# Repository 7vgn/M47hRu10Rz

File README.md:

# A Ruler with some mathematical extras

This is more than a regular ruler. It contains four mathematical topics from algebra, geometry, and other areas. Check out the [companion booklet](https://7vgn.github.io/M47hRu10Rz/). 

## Bill of Materials

| Ref | Qty | Part | Value | Links[^links]
| --- | ---:| --- | --- | --- |
| - | 1 | PCB | 2-layer, 0.8mm thickness, white soldermask, lead-free HASL | [J](https://jlcpcb.com/)
| C1 | 1 | Capacitor | SMD 1206, 100nF, X7R | [M](https://www.mouser.com/ProductDetail/?qs=Jm2GQyTW%2Fbgjukwx9JJFzw%3D%3D) [D](https://www.digikey.com/en/products/detail/kyocera-avx/KGM31DR72A104KU/563639?s=N4IgTCBcDaIIxgAwDY4GE6ICwGkCCAKmHiALoC%2BQA) [R](https://www.reichelt.de/shop/produkt/mlcc_1206_100_nf_100_v_-10_x7r-409241)
| D1..4 | 4 | LED | SMD 1206 (3216), green | [M](https://www.mouser.com/ProductDetail/?qs=kIhwFMorz7OTw%252BezAWlXhg%3D%3D) [D](https://www.digikey.com/en/products/detail/liteon/LTST-C150GKT/269216?s=N4IgTCBcDaIDIBUDKCC0BhAjAVgAwHEBpBEAXQF8g) [R](https://www.reichelt.de/shop/produkt/led_smd_1206_gruen_500_mcd_120_-361549)
| Q1[^polprot] | 1 | P-MOSFET | IRLML6402, SOT-23 | [M](https://www.mouser.com/ProductDetail/?qs=9%252BKlkBgLFf0HuZuONx2Ewg%3D%3D) [D](https://www.digikey.com/en/products/detail/infineon-technologies/IRLML6402TRPBF/811437) [R](https://www.reichelt.de/shop/produkt/mosfet_p-ch_-20v_-3_7a_0_065r_sot-23-108743)
| RN1..2 | 2 | Resistor Array | SMD 1206 (4x0603), 47kΩ | [M](https://www.mouser.com/ProductDetail/?qs=8cPjvKtxWv7ndzc71UR%252B8Q%3D%3D) [D](https://www.digikey.com/en/products/detail/yageo/YC164-JR-0747KL/1005161?s=N4IgTCBcDaIJoGECMA2ALAWgFICUMAYB2NQgaQBkQBdAXyA) [R](https://www.reichelt.de/shop/produkt/smd-widerstandsnetzwerk_1206_4x47_kohm_5_3_2x1_6x0_6_mm-42474)
| RN3..4 | 2 | Resistor Array | SMD 1206 (4x0603), 1kΩ | [M](https://www.mouser.com/ProductDetail/?qs=o9qB%2F%252BVTi4XY%252BFKU0Fetnw%3D%3D) [D](https://www.digikey.com/en/products/detail/yageo/YC164-JR-071KL/1005123?s=N4IgTCBcDaIJoGECMA2ALAWgFICUMAYB2JAaQBkQBdAXyA) [R](https://www.reichelt.de/shop/produkt/smd-widerstandsnetzwerk_1206_4x1_kohm_5_3_2x1_6x0_6_mm-42467)
| U1 | 1 | Quad CMOS NAND Gate | 74HC00PWR-Q100,118, TSSOP-20 | [M](https://www.mouser.com/ProductDetail/?qs=1sbE9T7hb3ZHx2CB2IdCWQ%3D%3D) [D](https://www.digikey.com/en/products/detail/nexperia-usa-inc/74HC00PW-Q100-118/3678826?s=N4IgTCBcDaIOwBYASBhADGgCgdQLQEUBGDAGkMIA4QBdAXyA)

[^links]: Links are just examples. Other sellers are available and similar parts can be substituted.  
[^polprot]: Q1 protects against reverse polarity and is optional. If left out, the solder jumper JP1 must be bridged instead. 

Required tools and materials: soldering iron, lead-free solder, hot-air station or hot plate, tweezers, flux, isopropyl alcohol for cleaning

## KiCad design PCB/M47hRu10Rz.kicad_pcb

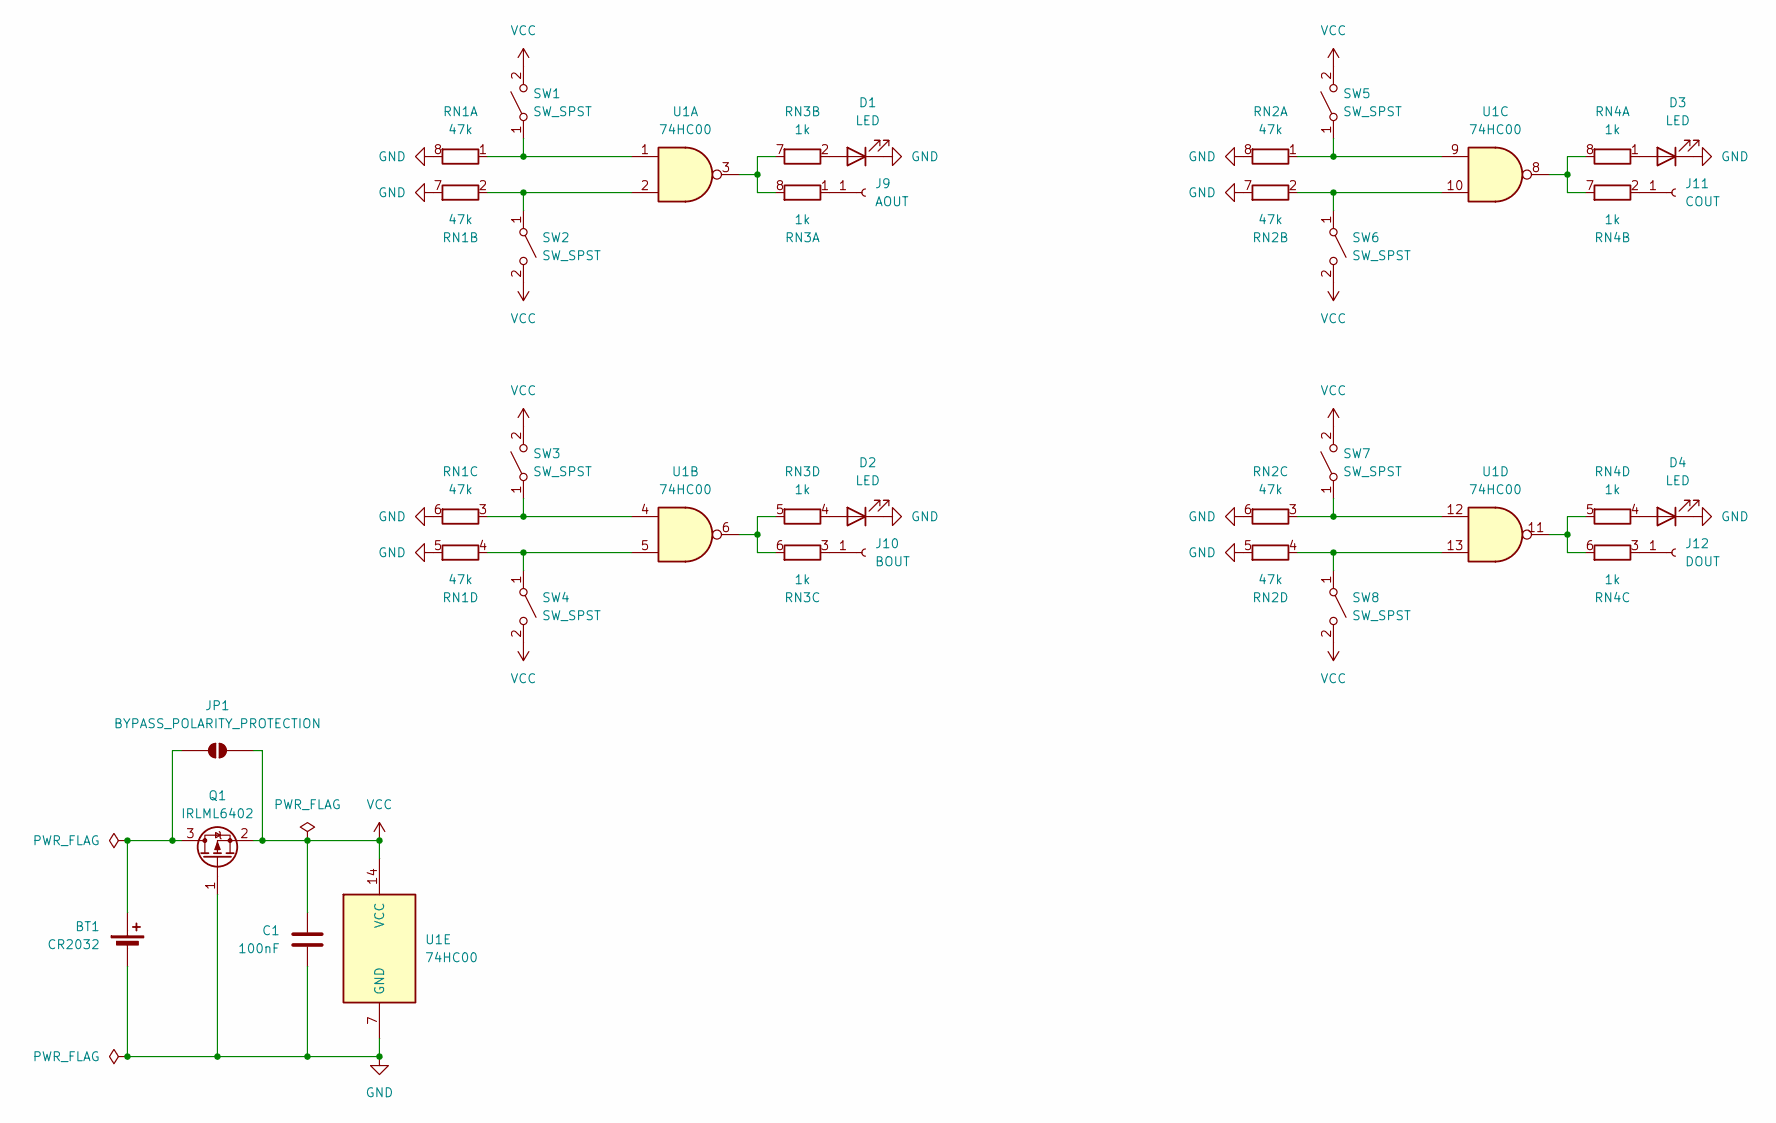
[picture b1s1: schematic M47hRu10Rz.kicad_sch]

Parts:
BT1: CR2032; Battery_CR2032
C1: 100nF; C_1206_3216Metric_Pad1.33x1.80mm_HandSolder
D1, D2, D3, D4: LED; LED_1206_3216Metric_Pad1.42x1.75mm_Arrow_HandSolder
J9: AOUT; ConnectionPoint
J10: BOUT; ConnectionPoint
J11: COUT; ConnectionPoint
J12: DOUT; ConnectionPoint
JP1: BYPASS_POLARITY_PROTECTION; SolderJumper-2_P1.3mm_Open_RoundedPad1.0x1.5mm
Q1: IRLML6402; SOT-23
RN1, RN2: 47k; R_Array_Convex_4x0603
RN3, RN4: 1k; R_Array_Convex_4x0603
SW1, SW2, SW3, SW4, SW5, SW6, SW7, SW8: SW_SPST; PaperclipButton
U1: 74HC00; TSSOP-14_4.4x5mm_P0.65mm

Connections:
GND: BT1.2 (-), C1.2, D1.1 (K), D2.1 (K), D3.1 (K), D4.1 (K), Q1.1 (G), RN1.5 (R4.2), RN1.6 (R3.2), RN1.7 (R2.2), RN1.8 (R1.2), RN2.5 (R4.2), RN2.6 (R3.2), RN2.7 (R2.2), RN2.8 (R1.2), U1.7 (GND)
unnamed: BT1.1 (+), JP1.1 (A), Q1.3 (D)
unnamed: D1.2 (A), RN3.2 (R2.1)
unnamed: D2.2 (A), RN3.4 (R4.1)
unnamed: D3.2 (A), RN4.1 (R1.1)
unnamed: D4.2 (A), RN4.4 (R4.1)
unnamed: J9.1 (Pin_1_1), RN3.1 (R1.1)
unnamed: J10.1 (Pin_1_1), RN3.3 (R3.1)
unnamed: J11.1 (Pin_1_1), RN4.2 (R2.1)
unnamed: J12.1 (Pin_1_1), RN4.3 (R3.1)
unnamed: RN1.1 (R1.1), SW1.1 (A), U1.1
unnamed: RN1.2 (R2.1), SW2.1 (A), U1.2
unnamed: RN1.3 (R3.1), SW3.1 (A), U1.4
unnamed: RN1.4 (R4.1), SW4.1 (A), U1.5
unnamed: RN2.1 (R1.1), SW5.1 (A), U1.9
unnamed: RN2.2 (R2.1), SW6.1 (A), U1.10
unnamed: RN2.3 (R3.1), SW7.1 (A), U1.12
unnamed: RN2.4 (R4.1), SW8.1 (A), U1.13
unnamed: RN3.7 (R2.2), RN3.8 (R1.2), U1.3
unnamed: RN3.5 (R4.2), RN3.6 (R3.2), U1.6
unnamed: RN4.7 (R2.2), RN4.8 (R1.2), U1.8
unnamed: RN4.5 (R4.2), RN4.6 (R3.2), U1.11
VCC: C1.1, JP1.2 (B), Q1.2 (S), SW1.2 (B), SW2.2 (B), SW3.2 (B), SW4.2 (B), SW5.2 (B), SW6.2 (B), SW7.2 (B), SW8.2 (B), U1.14 (VCC)

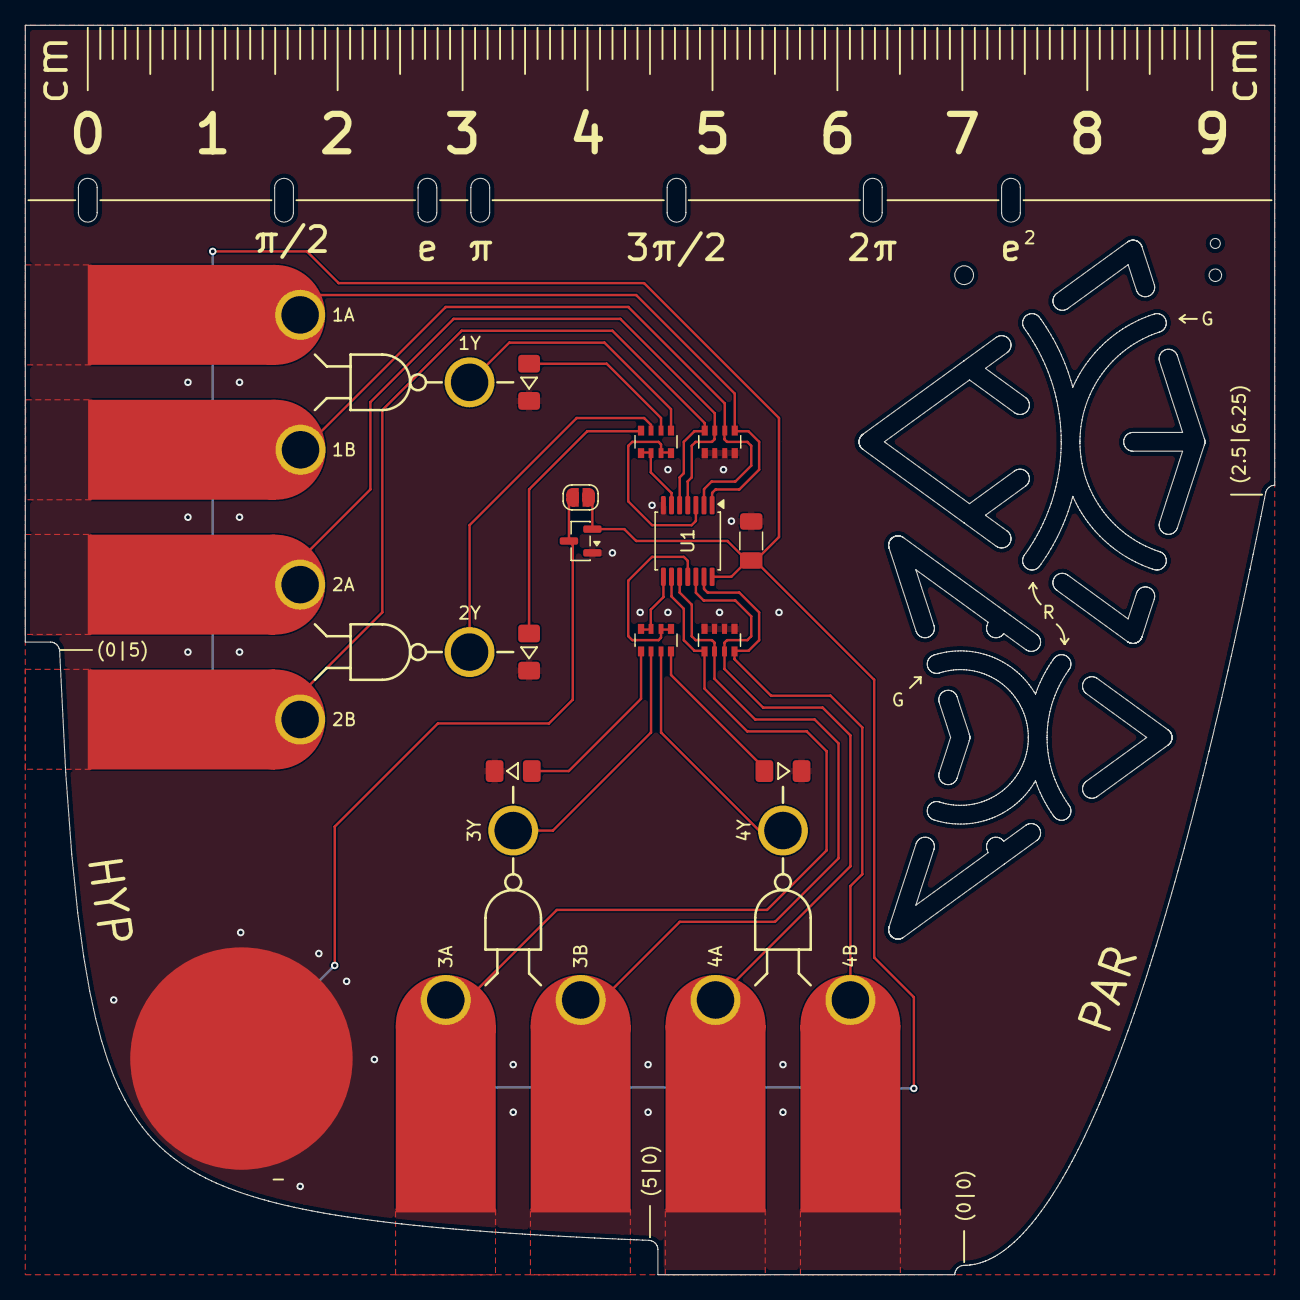
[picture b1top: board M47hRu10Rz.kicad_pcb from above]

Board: 2 copper layers, 100.0 x 100.0 mm, 25 parts (0 on the bottom side), 23 nets.
